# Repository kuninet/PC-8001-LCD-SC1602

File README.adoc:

= LCD SC1603 BOARD for PC-8001 

== 概要
* 16桁x2行のLCDモジュール SC1602(HD44780コンパチブル)をPC-8001拡張バスへ接続するボードです。

= ☆REV1 基板にはバグがあります☆
== アドレスデコーダーの配線に間違いがあります。ハード的に 74HC138の端子にジャンパ線を結ぶか、ソフトのパラメーターを工夫してください。m(_ _)m

image:image/working_image.jpg[]

== 説明
* PC-8001拡張バス(背面50ピン)にSC1602(HD44780コンパチブル)を接続するボードです。
* 74HC138でI/Oアドレスデコードします。$80〜や$90〜に設定がおすすめ。

== I/Oアドレス($90〜の場合)
* I/Oアドレスを$90〜とした場合、以下のようなアドレスとなります。

|===
|I/Oアドレス|RD/WR|説明

|$90
|WR
|各種設定

|$91
|WR
|CG RAM、DDRAMへデータ書き込み

|$92
|RD
|Busyフラグ、CG RAM、DDRAMアドレス読み出し

|$93
|RD
|CG RAM、DDRAMからデータ読み出し

|===

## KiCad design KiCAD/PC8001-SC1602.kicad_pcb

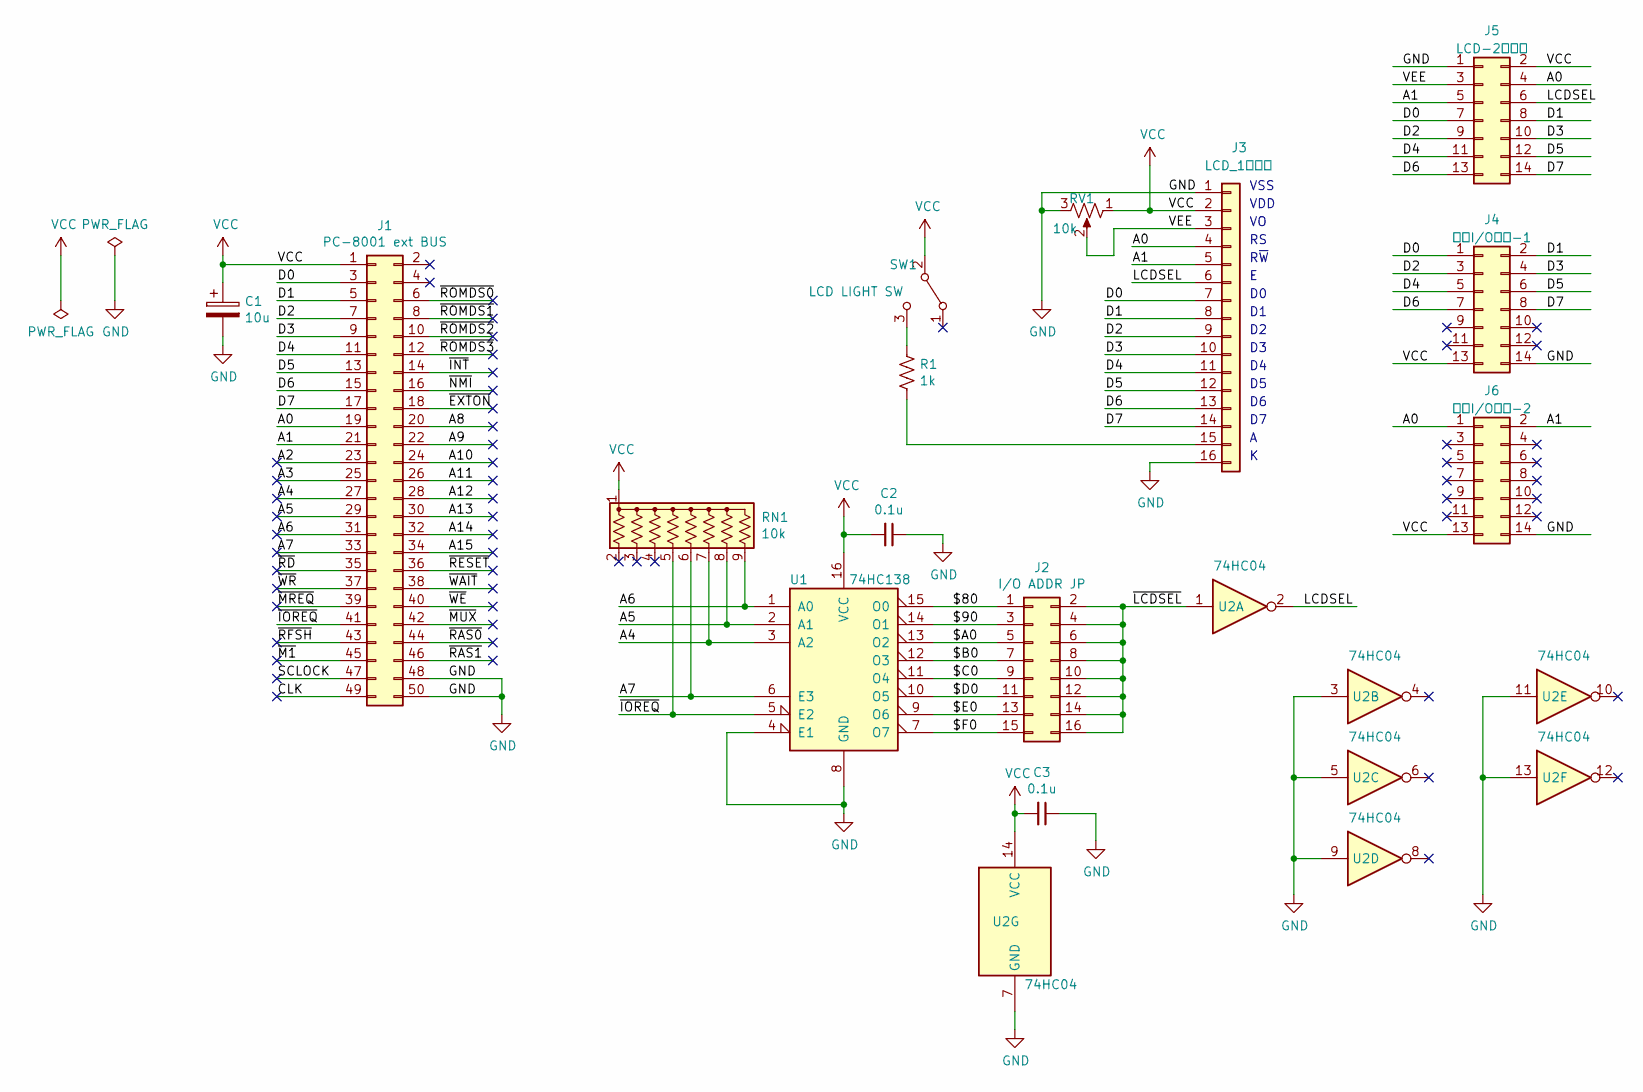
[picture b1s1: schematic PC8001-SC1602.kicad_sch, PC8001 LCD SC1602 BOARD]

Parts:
C1: 10u; CP_Radial_D5.0mm_P2.50mm
C2, C3: 0.1u; C_Disc_D3.0mm_W1.6mm_P2.50mm
J1: PC-8001 ext BUS; PinHeader_2x25_P2.54mm_Horizontal
J2: I/O ADDR JP; PinHeader_2x08_P2.54mm_Vertical
J3: LCD_1列端子; PinHeader_1x16_P2.54mm_Vertical
J4: 外部I/O端子-1; PinHeader_2x07_P2.54mm_Vertical
J5: LCD-2列端子; PinHeader_2x07_P2.54mm_Vertical
J6: 外部I/O端子-2; PinHeader_2x07_P2.54mm_Vertical
R1: 1k; R_Axial_DIN0207_L6.3mm_D2.5mm_P10.16mm_Horizontal
RN1: 10k; R_Array_SIP9
RV1: 10k; Potentiometer_Vishay_T73YP_Vertical
SW1: LCD LIGHT SW; PinHeader_1x03_P2.54mm_Vertical
U1: 74HC138; DIP-16_W7.62mm_Socket
U2: 74HC04; DIP-14_W7.62mm_Socket

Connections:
/$80: J2.1, U1.15 (O0)
/$90: J2.3, U1.14 (O1)
/$A0: J2.5, U1.13 (O2)
/$B0: J2.7, U1.12 (O3)
/$C0: J2.9, U1.11 (O4)
/$D0: J2.11, U1.10 (O5)
/$E0: J2.13, U1.9 (O6)
/A0: J1.19, J3.4, J5.4, J6.1
/A1: J1.21, J3.5, J5.5, J6.2
/A2: J1.23
/A3: J1.25
/A4: J1.27, RN1.7 (R6), U1.3 (A2)
/A5: J1.29, RN1.8 (R7), U1.2 (A1)
/A6: J1.31, RN1.9 (R8), U1.1 (A0)
/A7: J1.33, RN1.6 (R5), U1.6 (E3)
/A8: J1.20
/A9: J1.22
/A10: J1.24
/A11: J1.26
/A12: J1.28
/A13: J1.30
/A14: J1.32
/A15: J1.34
/CLK: J1.49
/D0: J1.3, J3.7, J4.1, J5.7
/D1: J1.5, J3.8, J4.2, J5.8
/D2: J1.7, J3.9, J4.3, J5.9
/D3: J1.9, J3.10, J4.4, J5.10
/D4: J1.11, J3.11, J4.5, J5.11
/D5: J1.13, J3.12, J4.6, J5.12
/D6: J1.15, J3.13, J4.7, J5.13
/D7: J1.17, J3.14, J4.8, J5.14
/LCDSEL: J3.6, J5.6, U2.2
/SCLOCK: J1.47
/VEE: J3.3, J5.3, RV1.2
/~EXTON: J1.18
/~INT: J1.14
/~IOREQ: J1.41, RN1.5 (R4), U1.5 (E2)
/~LCDSEL: J2.2, J2.4, J2.6, J2.8, J2.10, J2.12, J2.14, J2.16, U2.1
/~M1: J1.45
/~MREQ: J1.39
/~MUX: J1.42
/~NMI: J1.16
/~RAS0: J1.44
/~RAS1: J1.46
/~RD: J1.35
/~RESET: J1.36
/~RFSH: J1.43
/~ROMDS0: J1.6
/~ROMDS1: J1.8
/~ROMDS2: J1.10
/~ROMDS3: J1.12
/~WAIT: J1.38
/~WE: J1.40
/~WR: J1.37
GND: C1.2, C2.1, C3.1, J1.48, J1.50, J3.1, J3.16, J4.14, J5.1, J6.14, RV1.3, U1.4 (E1), U1.8 (GND), U2.3, U2.5, U2.7 (GND), U2.9, U2.11, U2.13
unnamed: J3.15, R1.2
unnamed: R1.1, SW1.3 (C)

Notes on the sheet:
VSS
VDD
R~{W}

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
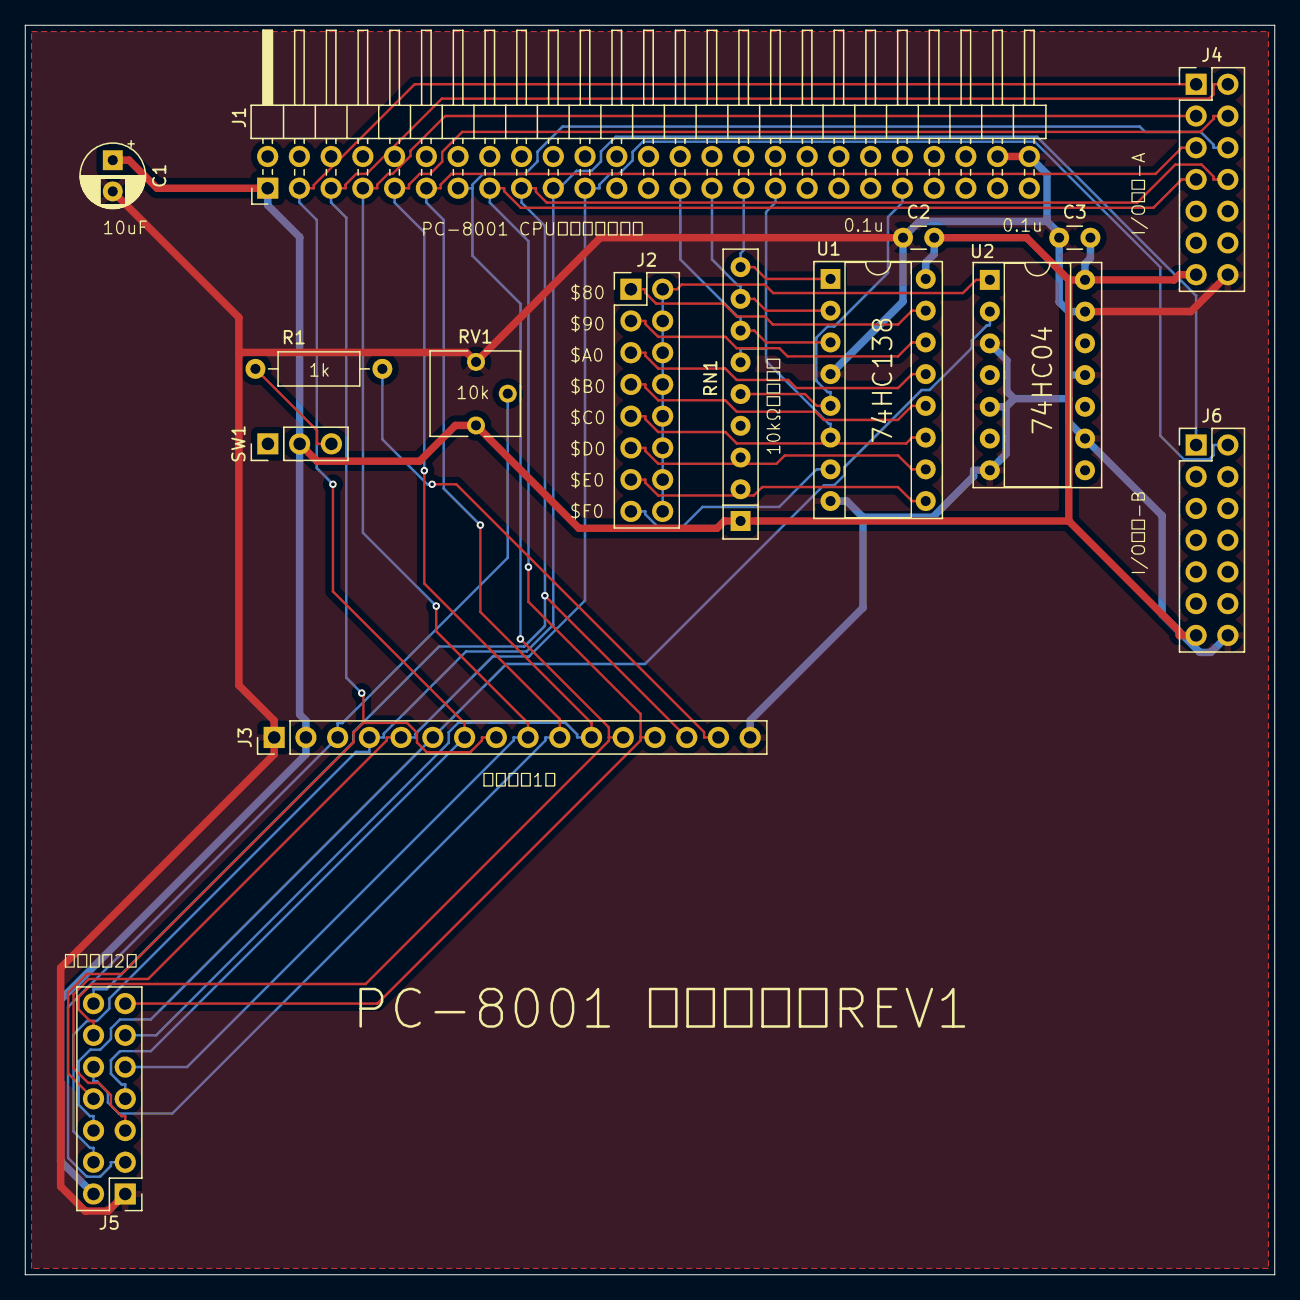
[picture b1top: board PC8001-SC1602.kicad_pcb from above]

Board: 2 copper layers, 100.0 x 100.0 mm, 15 parts (0 on the bottom side), 29 nets.

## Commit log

2020-02-11 init commit
2020-02-11 README等整備
2020-02-11 Create LICENSE
2020-02-11 回路図 微修正
2020-02-11 稼働イメージ画像添付
2020-02-11 readmeへ画像添付
2020-02-12 サンプルアプリ改良
2020-02-13 TL/1によるサンプル追加
2023-03-22 プリント基板データ作成 REV1
